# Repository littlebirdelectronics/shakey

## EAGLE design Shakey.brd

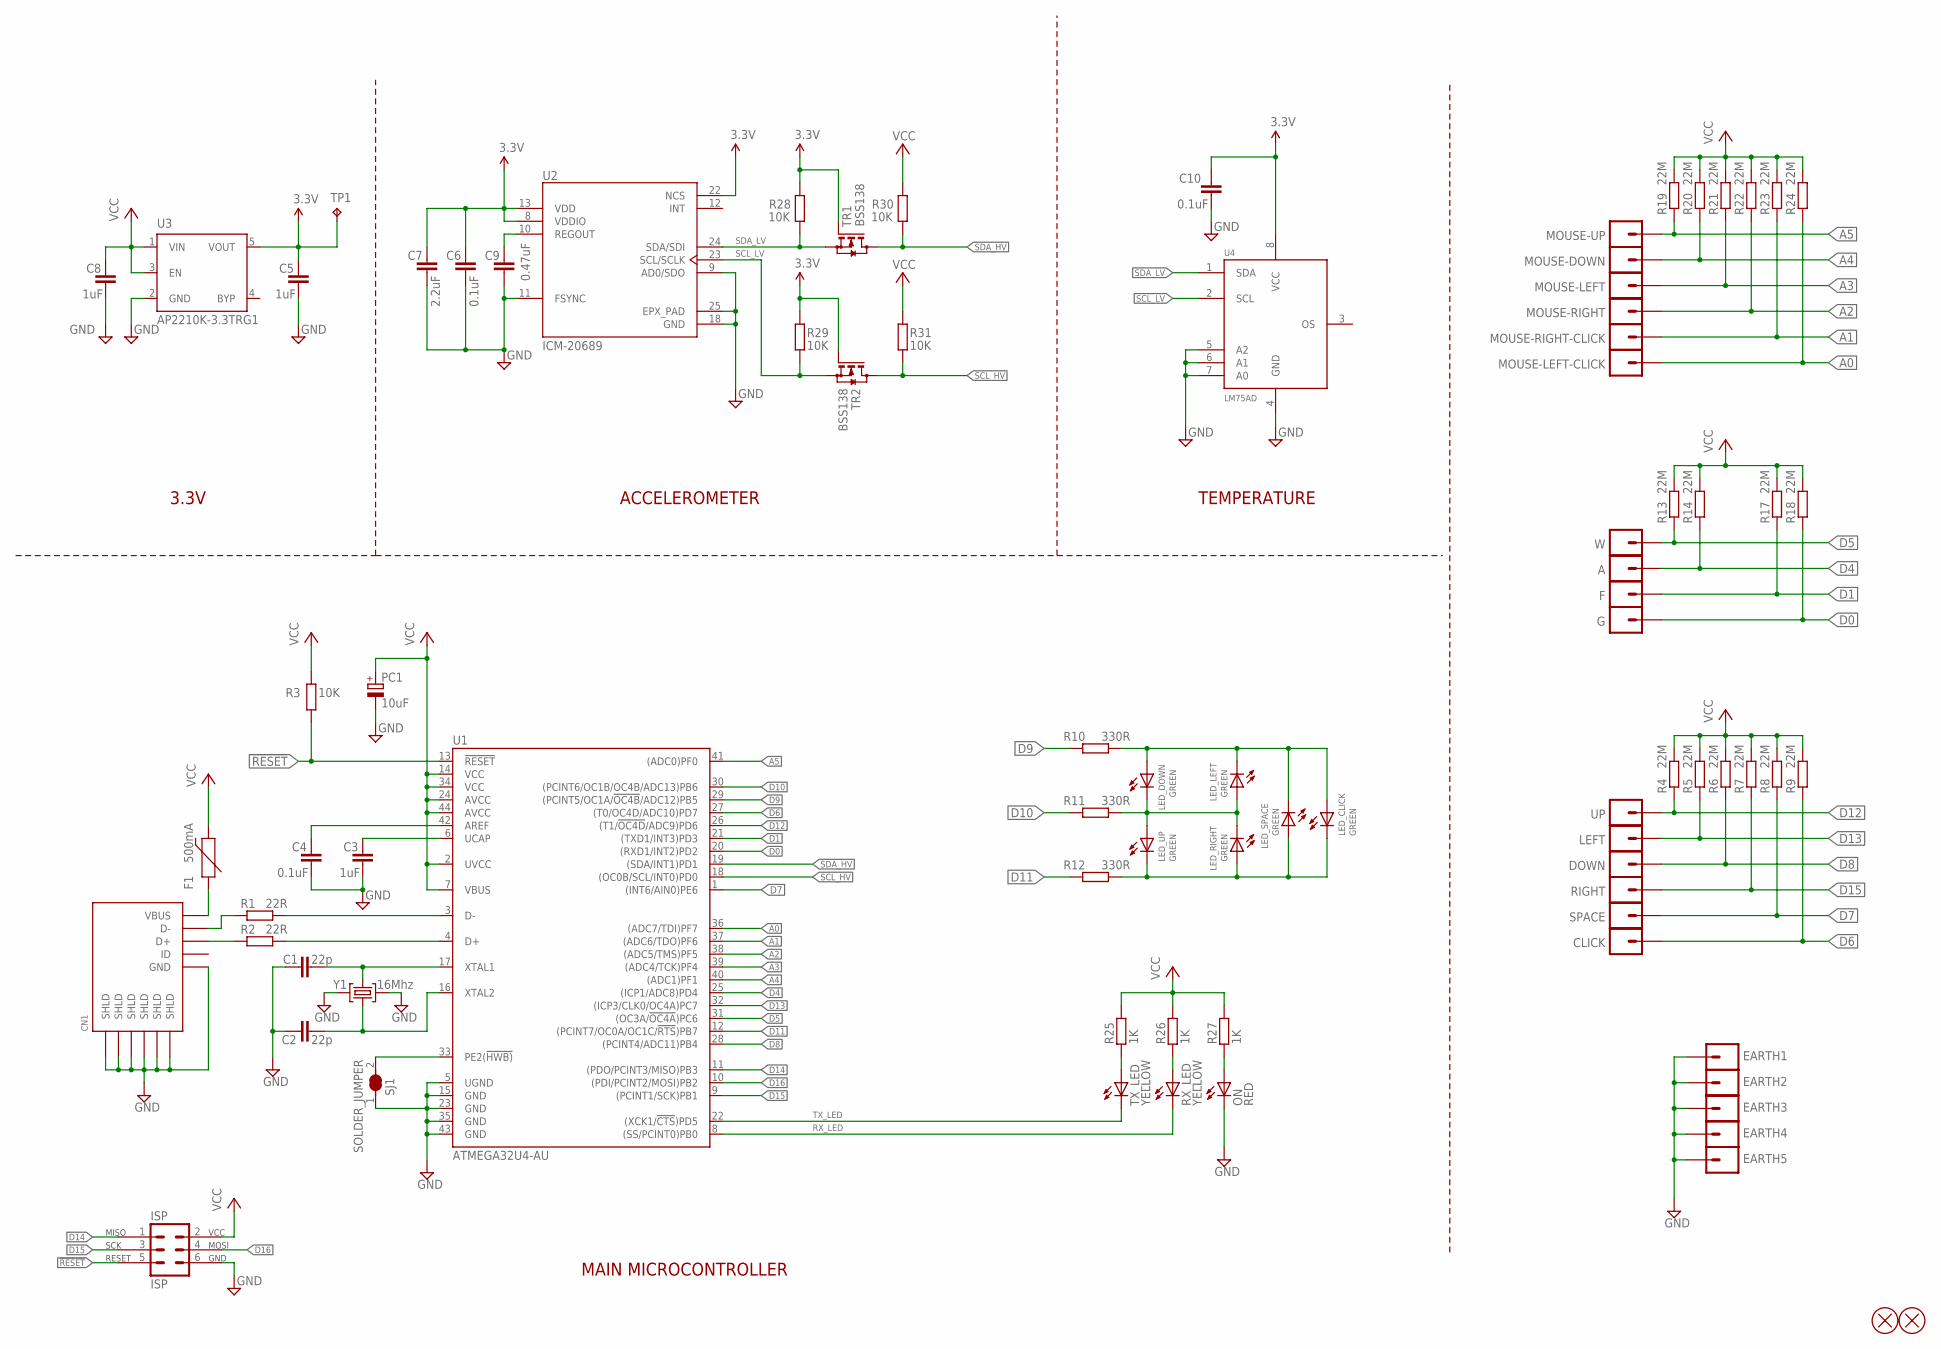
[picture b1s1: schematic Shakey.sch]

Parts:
A: MA01-1-ALLIGATOR-3.0MM
C1, C2: 22p; C0603; MPN C0603C220K4GACTU
C3, C5, C8: 1uF; C0603; MPN CL10A105KA8NNNC
C4, C6, C10: 0.1uF; C0603; MPN CL10B104KB8NNNC
C7: 2.2uF; C0603; MPN CL10A225KO8NNNC
C9: 0.47uF; C0603; MPN GCM188R71C474KA55D
CLICK: MA01-1-ALLIGATOR-3.0MM
CN1: MicroUSB; 4UCON-11071
DOWN: MA01-1-ALLIGATOR-3.0MM
EARTH1, EARTH2, EARTH3, EARTH4, EARTH5: MA01-1-ALLIGATOR-3.0MM
F: MA01-1-ALLIGATOR-3.0MM
F1: 500mA; PPC-1206; MPN 0ZCJ0050FF2G
G: MA01-1-ALLIGATOR-3.0MM
ISP: ISP; MA03-2
JP1, JP2: FIDUCIAL-1X3MM
LED_CLICK: GREEN; LED-1206-LTST-BOTTOM; MPN LTST-C230KGKT
LED_DOWN: GREEN; LED-1206-LTST-BOTTOM; MPN LTST-C230KGKT
LED_LEFT: GREEN; LED-1206-LTST-BOTTOM; MPN LTST-C230KGKT
LED_RIGHT: GREEN; LED-1206-LTST-BOTTOM; MPN LTST-C230KGKT
LED_SPACE: GREEN; LED-1206-LTST-BOTTOM; MPN LTST-C230KGKT
LED_UP: GREEN; LED-1206-LTST-BOTTOM; MPN LTST-C230KGKT
LEFT: MA01-1-ALLIGATOR-3.0MM
MOUSE-DOWN: MA01-1-ALLIGATOR-3.0MM
MOUSE-LEFT: MA01-1-ALLIGATOR-3.0MM
MOUSE-LEFT-CLICK: MA01-1-ALLIGATOR-3.0MM
MOUSE-RIGHT: MA01-1-ALLIGATOR-3.0MM
MOUSE-RIGHT-CLICK: MA01-1-ALLIGATOR-3.0MM
MOUSE-UP: MA01-1-ALLIGATOR-3.0MM
ON: RED; LED-1206-LTST-BOTTOM; MPN LTST-C230KRKT
PC1: 10uF; CT6032; MPN T491C106K020AT7280
R1, R2: 22R; R0603; MPN RMCF0603JT22R0
R3, R28, R29, R30, R31: 10K; R0603; MPN RMCF0603JG10K0
R4, R5, R6, R7, R8, R9, R13, R14, R17, R18, R19, R20, R21, R22, R23, R24: 22M; R0603; MPN ERJ-3GEYK226V
R10, R11, R12: 330R; R0603; MPN RMCF0603JT330R
R25, R26, R27: 1K; R0603; MPN RC0603JR-071KL
RIGHT: MA01-1-ALLIGATOR-3.0MM
RX_LED: YELLOW; LED-1206-LTST-BOTTOM; MPN LTST-C230KSKT
SJ1: SOLDER_JUMPER; SOLDER_JUMPER_NC
SPACE: MA01-1-ALLIGATOR-3.0MM
TP1: TESTPAD; TP-2.54MM
TR1, TR2: BSS138; SOT23; MPN BSS138
TX_LED: YELLOW; LED-1206-LTST-BOTTOM; MPN LTST-C230KSKT
U1: ATMEGA32U4-AU; TQFP44
U2: ICM-20689; QFN-24-4X4-0.9MM; MPN ICM-20689
U3: AP2210K-3.3TRG1; SOT23-5
U4: LM75AD; SOT96-1; MPN LM75AD,118
UP: MA01-1-ALLIGATOR-3.0MM
W: MA01-1-ALLIGATOR-3.0MM
Y1: 16Mhz; FA-238; MPN FA-238 16.0000MB-C3

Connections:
3.3V: C5.2, C6.2, C7.2, C10.2, R28.2, R29.2, TP1.TP, TR1.1 (G), TR2.1 (G), U2.8 (VDDIO), U2.13 (VDD), U2.22 (NCS), U3.5 (VOUT), U4.8 (VCC)
!RESET!: ISP.5, R3.1, U1.13 (!RESET)
A0: MOUSE-LEFT-CLICK.1@0, MOUSE-LEFT-CLICK.1@1, R24.1, U1.36 ((ADC7/TDI)PF7)
A1: MOUSE-RIGHT-CLICK.1@0, MOUSE-RIGHT-CLICK.1@1, R23.1, U1.37 ((ADC6/TDO)PF6)
A2: MOUSE-RIGHT.1@0, MOUSE-RIGHT.1@1, R22.1, U1.38 ((ADC5/TMS)PF5)
A3: MOUSE-LEFT.1@0, MOUSE-LEFT.1@1, R21.1, U1.39 ((ADC4/TCK)PF4)
A4: MOUSE-DOWN.1@0, MOUSE-DOWN.1@1, R20.1, U1.40 ((ADC1)PF1)
A5: MOUSE-UP.1@0, MOUSE-UP.1@1, R19.1, U1.41 ((ADC0)PF0)
D0: G.1@0, G.1@1, R18.1, U1.20 ((RXD1/INT2)PD2)
D1: F.1@0, F.1@1, R17.1, U1.21 ((TXD1/INT3)PD3)
D4: A.1@0, A.1@1, R14.1, U1.25 ((ICP1/ADC8)PD4)
D5: R13.1, U1.31 ((OC3A/!OC4A!)PC6), W.1@0, W.1@1
D6: CLICK.1@0, CLICK.1@1, R9.1, U1.27 ((T0/OC4D/ADC10)PD7)
D7: R8.1, SPACE.1@0, SPACE.1@1, U1.1 ((INT6/AIN0)PE6)
D8: DOWN.1@0, DOWN.1@1, R6.1, U1.28 ((PCINT4/ADC11)PB4)
D9: R10.1, U1.29 ((PCINT5/OC1A/!OC4B!/ADC12)PB5)
D10: R11.1, U1.30 ((PCINT6/OC1B/OC4B/ADC13)PB6)
D11: R12.1, U1.12 ((PCINT7/OC0A/OC1C/!RTS!)PB7)
D12: R4.1, U1.26 ((T1/!OC4D!/ADC9)PD6), UP.1@0, UP.1@1
D13: LEFT.1@0, LEFT.1@1, R5.1, U1.32 ((ICP3/CLK0/OC4A)PC7)
D14: ISP.1, U1.11 ((PDO/PCINT3/MISO)PB3)
D15: ISP.3, R7.1, RIGHT.1@0, RIGHT.1@1, U1.9 ((PCINT1/SCK)PB1)
D16: ISP.4, U1.10 ((PDI/PCINT2/MOSI)PB2)
GND: C1.1, C2.1, C3.1, C4.1, C5.1, C6.1, C7.1, C8.1, C9.1, C10.1, CN1.GND, CN1.SHLD@1 (SHLD), CN1.SHLD@2 (SHLD), CN1.SHLD@3 (SHLD), CN1.SHLD@4 (SHLD), CN1.SHLD@5 (SHLD), CN1.SHLD@6 (SHLD), EARTH1.1@0, EARTH1.1@1, EARTH2.1@0, EARTH2.1@1, EARTH3.1@0, EARTH3.1@1, EARTH4.1@0, EARTH4.1@1, EARTH5.1@0, EARTH5.1@1, ISP.6, ON.C, PC1.-, SJ1.1, U1.5 (UGND), U1.15 (GND), U1.23 (GND), U1.35 (GND), U1.43 (GND), U2.9 (AD0/SDO), U2.11 (FSYNC), U2.18 (GND), U2.25 (EPX_PAD), U3.2 (GND), U4.4 (GND), U4.5 (A2), U4.6 (A1), U4.7 (A0), Y1.2, Y1.4
HWB: SJ1.2, U1.33 (PE2(!HWB))
unnamed: C4.2, U1.42 (AREF)
unnamed: C1.2, U1.17 (XTAL1), Y1.1
unnamed: C2.2, U1.16 (XTAL2), Y1.3
unnamed: LED_CLICK.A, LED_DOWN.A, LED_LEFT.C, LED_SPACE.C, R10.2
unnamed: CN1.VBUS, F1.1
unnamed: C3.2, U1.6 (UCAP)
unnamed: CN1.D-, R1.1
unnamed: R1.2, U1.3 (D-)
unnamed: R2.2, U1.4 (D+)
unnamed: CN1.D+, R2.1
unnamed: LED_CLICK.C, LED_RIGHT.A, LED_SPACE.A, LED_UP.C, R12.2
unnamed: LED_DOWN.C, LED_LEFT.A, LED_RIGHT.C, LED_UP.A, R11.2
unnamed: C9.2, U2.10 (REGOUT)
unnamed: R25.1, TX_LED.A
unnamed: R26.1, RX_LED.A
unnamed: ON.A, R27.1
RX_LED: RX_LED.C, U1.8 ((SS/PCINT0)PB0)
SCL_HV: R31.1, TR2.3 (D), U1.18 ((OC0B/SCL/INT0)PD0)
SCL_LV: R29.1, TR2.2 (S), U2.23 (SCL/SCLK), U4.2 (SCL)
SDA_HV: R30.1, TR1.3 (D), U1.19 ((SDA/INT1)PD1)
SDA_LV: R28.1, TR1.2 (S), U2.24 (SDA/SDI), U4.1 (SDA)
TX_LED: TX_LED.C, U1.22 ((XCK1/!CTS!)PD5)
VCC: C8.2, F1.2, ISP.2, PC1.+, R3.2, R4.2, R5.2, R6.2, R7.2, R8.2, R9.2, R13.2, R14.2, R17.2, R18.2, R19.2, R20.2, R21.2, R22.2, R23.2, R24.2, R25.2, R26.2, R27.2, R30.2, R31.2, U1.2 (UVCC), U1.7 (VBUS), U1.14 (VCC), U1.24 (AVCC), U1.34 (VCC), U1.44 (AVCC), U3.1 (VIN), U3.3 (EN)

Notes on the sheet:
ACCELEROMETER
TEMPERATURE
3.3V
MAIN MICROCONTROLLER

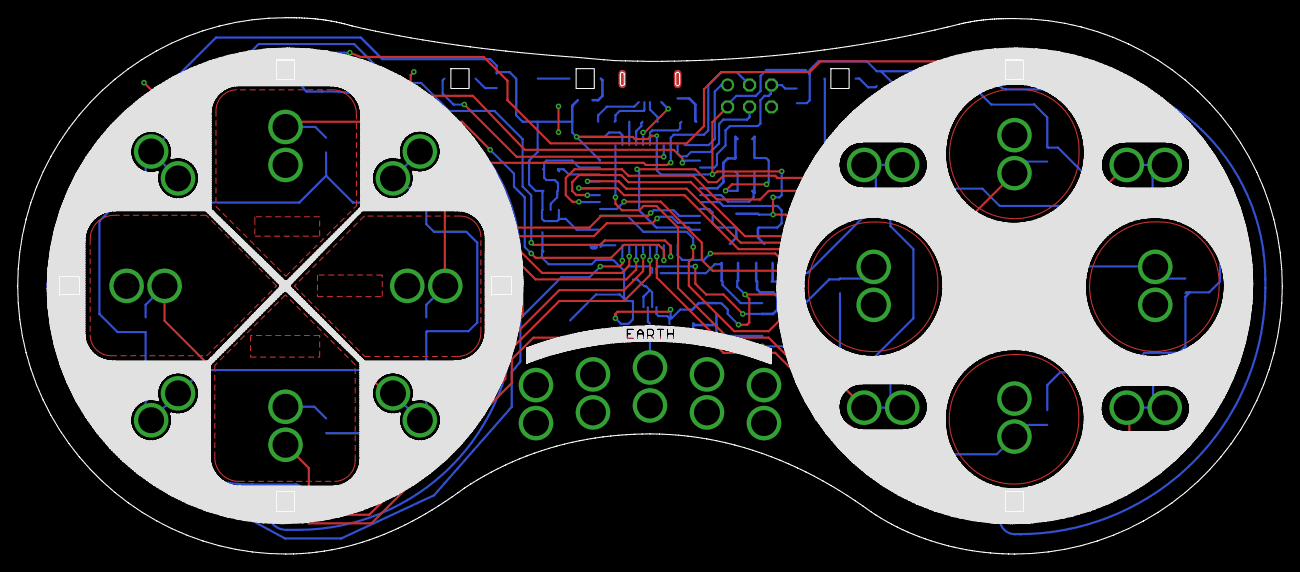
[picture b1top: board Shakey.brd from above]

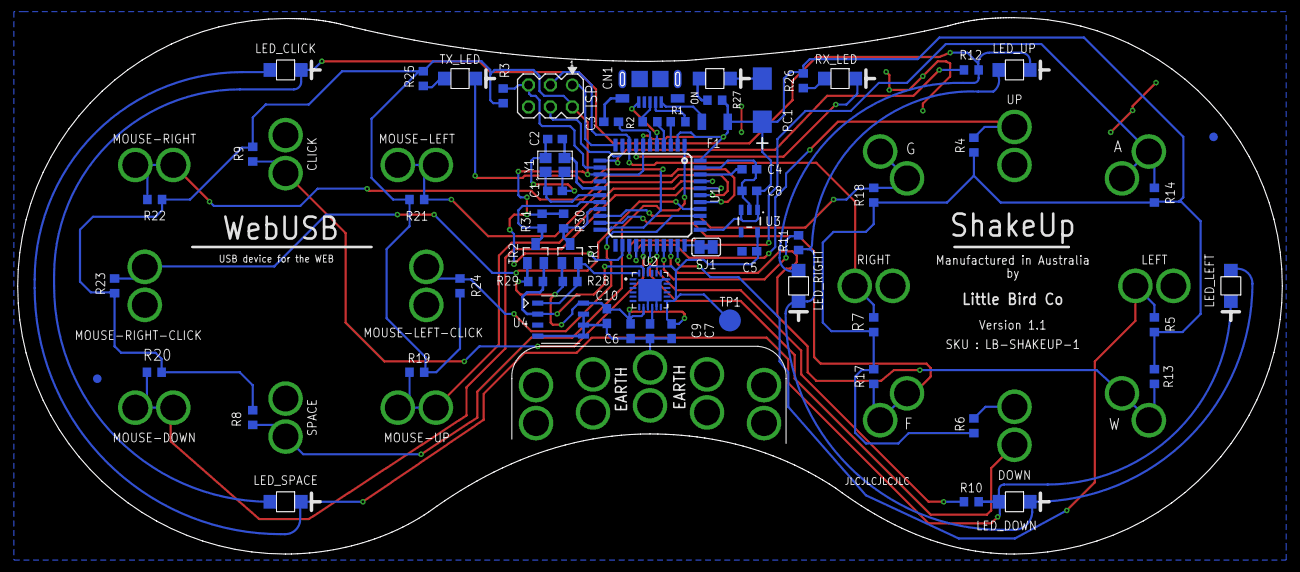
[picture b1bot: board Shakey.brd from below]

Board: 2 copper layers, 146.4 x 62.1 mm, 84 parts (84 on the bottom side), 48 nets.

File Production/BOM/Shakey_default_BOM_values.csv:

"Qty";"Value";"Device";"Parts";"Library";"LibraryDescription";"DESCRIPTION";"MF";"MPN";"OC_DIGIKEY";"SUPPLIER";"UNITPRICE";"URL";
"1";"AP2210K-3.3TRG1";"AP2210K-3.3TRG1";"U3";"SixthLogic";"The AP2210 is a 300mA ULDO regulator which provides very low";"IC REG LDO 3.3V 0.3A SOT23-5";"Diodes Inc";"AP2210K-3.3TRG1";"AP2210K-3.3TRG1DITR-ND";"";"$0.10797";"https://www.digikey.com/product-detail/en/diodes-incorporate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";
"1";"ATMEGA32U4-AU";"ATMEGA32U4-AU";"U1";"SixthLogic";"Atmel ATmega32u4 MCU, 32KByte";"IC MCU 8BIT 32KB FLASH";"Microchip Technology";"ATMEGA32U4-AU";"ATMEGA32U4-AU-ND";"";"$3.04";"https://www.digikey.com/product-detail/en/microchip-technolo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";
"3";"0.1uF";"C-EUC0603";"C4, C6, C10";"rcl";"CAPACITOR, European symbol";"CAP CER 0.1UF 50V X7R 0603";"Samsung Electro-Mechanics";"CL10B104KB8NNNC";"1276-1000-2-ND";"Digikey";"$0.00652";"https://www.digikey.com/product-detail/en/samsung-electro-me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";
"1";"0.47uF";"C-EUC0603";"C9";"rcl";"CAPACITOR, European symbol";"CAP CER 0.47UF 16V X7R 0603";"Murata Electronics North America";"GCM188R71C474KA55D";"490-4775-2-ND";"Digikey";"$0.03744";"https://www.digikey.com/product-detail/en/murata-electronics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";
"3";"1uF";"C-EUC0603";"C3, C5, C8";"rcl";"CAPACITOR, European symbol";"CAP CER 1UF 25V X5R 0603";"Samsung Electro-Mechanics";"CL10A105KA8NNNC";"1276-1102-2-ND";"Digikey";"$0.00785";"https://www.digikey.com/product-detail/en/samsung-electro-me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";
"1";"2.2uF";"C-EUC0603";"C7";"rcl";"CAPACITOR, European symbol";"CAP CER 2.2UF 16V X5R 0603";"Samsung Electro-Mechanics";"CL10A225KO8NNNC";"1276-1040-2-ND";"Digikey";"$0.01863";"https://www.digikey.com/product-detail/en/samsung-electro-me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";
"2";"22p";"C-EUC0603";"C1, C2";"rcl";"CAPACITOR, European symbol";"CAP CER 22PF 16V C0G/NP0 0603";"KEMET";"C0603C220K4GACTU";"399-9031-2-ND";"Digikey";"$0.01675";"https://www.digikey.com/product-detail/en/kemet/C0603C220K4G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";
"1";"10uF";"CAP_POL-CT6032";"PC1";"SixthLogic";"Capacitor with Polarity";"CAP TANT 10UF 20V 10% 2312";"KEMET";"T491C106K020AT7280";"399-10158-2-ND";"Digikey";"$0.15113";"https://www.digikey.com/product-detail/en/kemet/T491C106K020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";
"1";"MicroUSB";"CONN_USB-4UCON-11071";"CN1";"SixthLogic";"USB Connector";"B TYPE FEMALE 05P SMT 90° WITHOUT POST 2 SHELL TABS";"4UCON";"11071";"";"";"";"http://www.4uconnector.com/online/Itemadrawing.asp?fldseries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";
"1";"16Mhz";"CRYSTAL_GROUNDED_2GND-FA-238";"Y1";"SixthLogic";"4 PIN SMD Crystal";"CRYSTAL 16.0000MHZ 18PF SMD";"EPSON";"FA-238 16.0000MB-C3";"SER3686TR-ND";"Digikey";"$0.22880";"https://www.digikey.com/product-detail/en/epson/FA-238-16.00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";
"1";"ISP";"DEBUGPORT-6PIN-ISP-AVR";"ISP";"SixthLogic";"";"6 Pin ISP port";"";"";"";"";"";"";
"2";"FIDUCIAL-1X3MM";"FIDUCIAL-1X3MM";"JP1, JP2";"SixthLogic";"";"";"";"";"";"";"";"";
"1";"ICM-20689";"ICM-20689";"U2";"SixthLogic";"High Performance 6-Axis MEMS MotionTracking Device in 4x4 mm Package";"IMU ACCEL/GYRO/TEMP I2C/SPI QFN";"TDK InvenSense";"ICM-20689";"1428-1059-2-ND";"Digikey";"$2.62548";"https://www.digikey.com/product-detail/en/tdk-invensense/ICM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";
"6";"GREEN";"LED-1206-LTST-BOTTOM";"LED_CLICK, LED_DOWN, LED_LEFT, LED_RIGHT, LED_SPACE, LED_UP";"SixthLogic";"";"LED GREEN CLEAR CHIP SMD";"Lite-On Inc.";"LTST-C230KGKT";"160-1456-2-ND";"Digikey";"$0.05693";"https://www.digikey.com/product-detail/en/lite-on-inc/LTST-C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";
"1";"RED";"LED-1206-LTST-BOTTOM";"ON";"SixthLogic";"";"LED RED CLEAR CHIP SMD";"Lite-On Inc.";"LTST-C230KRKT";"160-1457-2-ND";"Digikey";"$0.05668";"https://www.digikey.com/product-detail/en/lite-on-inc/LTST-C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";
"2";"YELLOW";"LED-1206-LTST-BOTTOM";"RX_LED, TX_LED";"SixthLogic";"";"LED YELLOW CLEAR CHIP SMD";"Lite-On Inc.";"LTST-C230KSKT";"160-1458-2-ND";"Digikey";"$0.05595";"https://www.digikey.com/product-detail/en/lite-on-inc/LTST-C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";
"1";"LM75AD";"LM75AD";"U4";"SixthLogic";"LM75";"SENSOR DIGITAL -55C-125C 8SO";"NXP USA Inc.";"LM75AD,118";"568-10295-2-ND";"Digikey";"$0.28743";"https://www.digikey.com/product-detail/en/nxp-usa-inc/LM75AD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";
"21";"";"MA01-1-ALLIGATOR-3.0MM";"A, CLICK, DOWN, EARTH1, EARTH2, EARTH3, EARTH4, EARTH5, F, G, LEFT, MOUSE-DOWN, MOUSE-LEFT, MOUSE-LEFT-CLICK, MOUSE-RIGHT, MOUSE-RIGHT-CLICK, MOUSE-UP, RIGHT, SPACE, UP, W";"SixthLogic";"2x Holes for Alligator Clips";"2x3mm Holes for Alligator Clips ";"";"";"";"";"";"";
"2";"BSS138";"MOSFET-N-BSS138";"TR1, TR2";"SixthLogic";"";"MOSFET N-CH 50V 220MA SOT-23";"ON Semiconductor";"BSS138";"BSS138TR-ND";"Digikey";"$0.05419";"https://www.digikey.com/product-detail/en/on-semiconductor/B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";
"1";"500mA";"PPTC-1206";"F1";"SixthLogic";"";"PTC RESET FUSE 8V 500MA 1206";"Bel Fuse Inc.";"0ZCJ0050FF2G";"507-1802-6-ND";"Digikey";"$0.07588";"https://www.digikey.com/product-detail/en/bel-fuse-inc/0ZCJ0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";
"5";"10K";"R-EU_R0603";"R3, R28, R29, R30, R31";"rcl";"RESISTOR, European symbol";"RES 10K OHM 5% 1/10W 0603";"Stackpole Electronics Inc.";"RMCF0603JG10K0";"RMCF0603JG10K0TR-ND";"Digikey";"$0.00170";"https://www.digikey.com/product-detail/en/stackpole-electron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";
"3";"1K";"R-EU_R0603";"R25, R26, R27";"rcl";"RESISTOR, European symbol";"RES SMD 1K OHM 5% 1/10W 0603";"Yageo";"RC0603JR-071KL";"311-1.0KGRTR-ND";"Digikey";"$0.00268";"https://www.digikey.com/product-detail/en/yageo/RC0603JR-071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";
"16";"22M";"R-EU_R0603";"R4, R5, R6, R7, R8, R9, R13, R14, R17, R18, R19, R20, R21, R22, R23, R24";"rcl";"RESISTOR, European symbol";"RES SMD 22M OHM 10% 1/10W 0603";"Panasonic Electronic Components";"ERJ-3GEYK226V";"P22MGTR-ND";"Digikey";"$0.00335";"https://www.digikey.com/product-detail/en/panasonic-electron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";
"2";"22R";"R-EU_R0603";"R1, R2";"rcl";"RESISTOR, European symbol";"RES 22 OHM 5% 1/10W 0603";"Stackpole Electronics Inc.";"RMCF0603JT22R0";"RMCF0603JT22R0TR-ND";"Digikey";"$0.00196";"https://www.digikey.com/product-detail/en/stackpole-electron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";
"3";"330R";"R-EU_R0603";"R10, R11, R12";"rcl";"RESISTOR, European symbol";"RES 330 OHM 5% 1/10W 0603";"Stackpole Electronics Inc.";"RMCF0603JT330R";"RMCF0603JT330RTR-ND";"Digikey";"$0.00196";"https://www.digikey.com/product-detail/en/stackpole-electron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";
"1";"SOLDER_JUMPER";"SOLDER_JUMPER_NC";"SJ1";"SixthLogic";"Solder Jumper - Normally Closed";"Solder Jumper - Normally Closed";"";"";"";"";"";"";
"1";"TESTPAD";"TESTPAD-2.54MM";"TP1";"SixthLogic";"";"";"";"";"";"";"";"";

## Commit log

2018-09-06 completed basic schematic
2018-09-07 completed schematic
2018-09-07 rearranged level shifter
2018-09-08 added controller outline
2018-09-10 added LM75
2018-09-12 90 percent parts placed
2018-09-12 completed arranging parts
2018-09-13 50 percent tracks done
2018-09-14 finished tracks
2018-09-14 working on silkscreen design
2018-09-18 completed
2018-09-20 sent board for prototyping
2018-09-21 added BOM with attributes
2018-10-24 added fiducial, branding text,logo
2018-10-26 added Australian Made logo, adjusted some text to make them even
2018-10-26 updated expenses files
2018-11-06 ready for production
2018-11-07 generated production gerber
2018-11-09 added Australian Made Logo
2018-11-12 changed croc hole to 3.0mm
2018-12-04 correct Micro USB value for P&P
2019-03-15 added part value for P&P
2019-03-15 added Testjig images
2019-03-22 getting ready to port to github
2019-04-15 added Production test folder
2019-06-05 changed name to ShakeUp
